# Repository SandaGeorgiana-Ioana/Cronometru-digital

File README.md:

Schema electronică 

Cablaj imprimat

Asamplare PCB

Poza finală după ce am lipit piesele și l-am alimentat

[Documentație.pdf](https://github.com/user-attachments/files/19416694/Documenta.ie.pdf)

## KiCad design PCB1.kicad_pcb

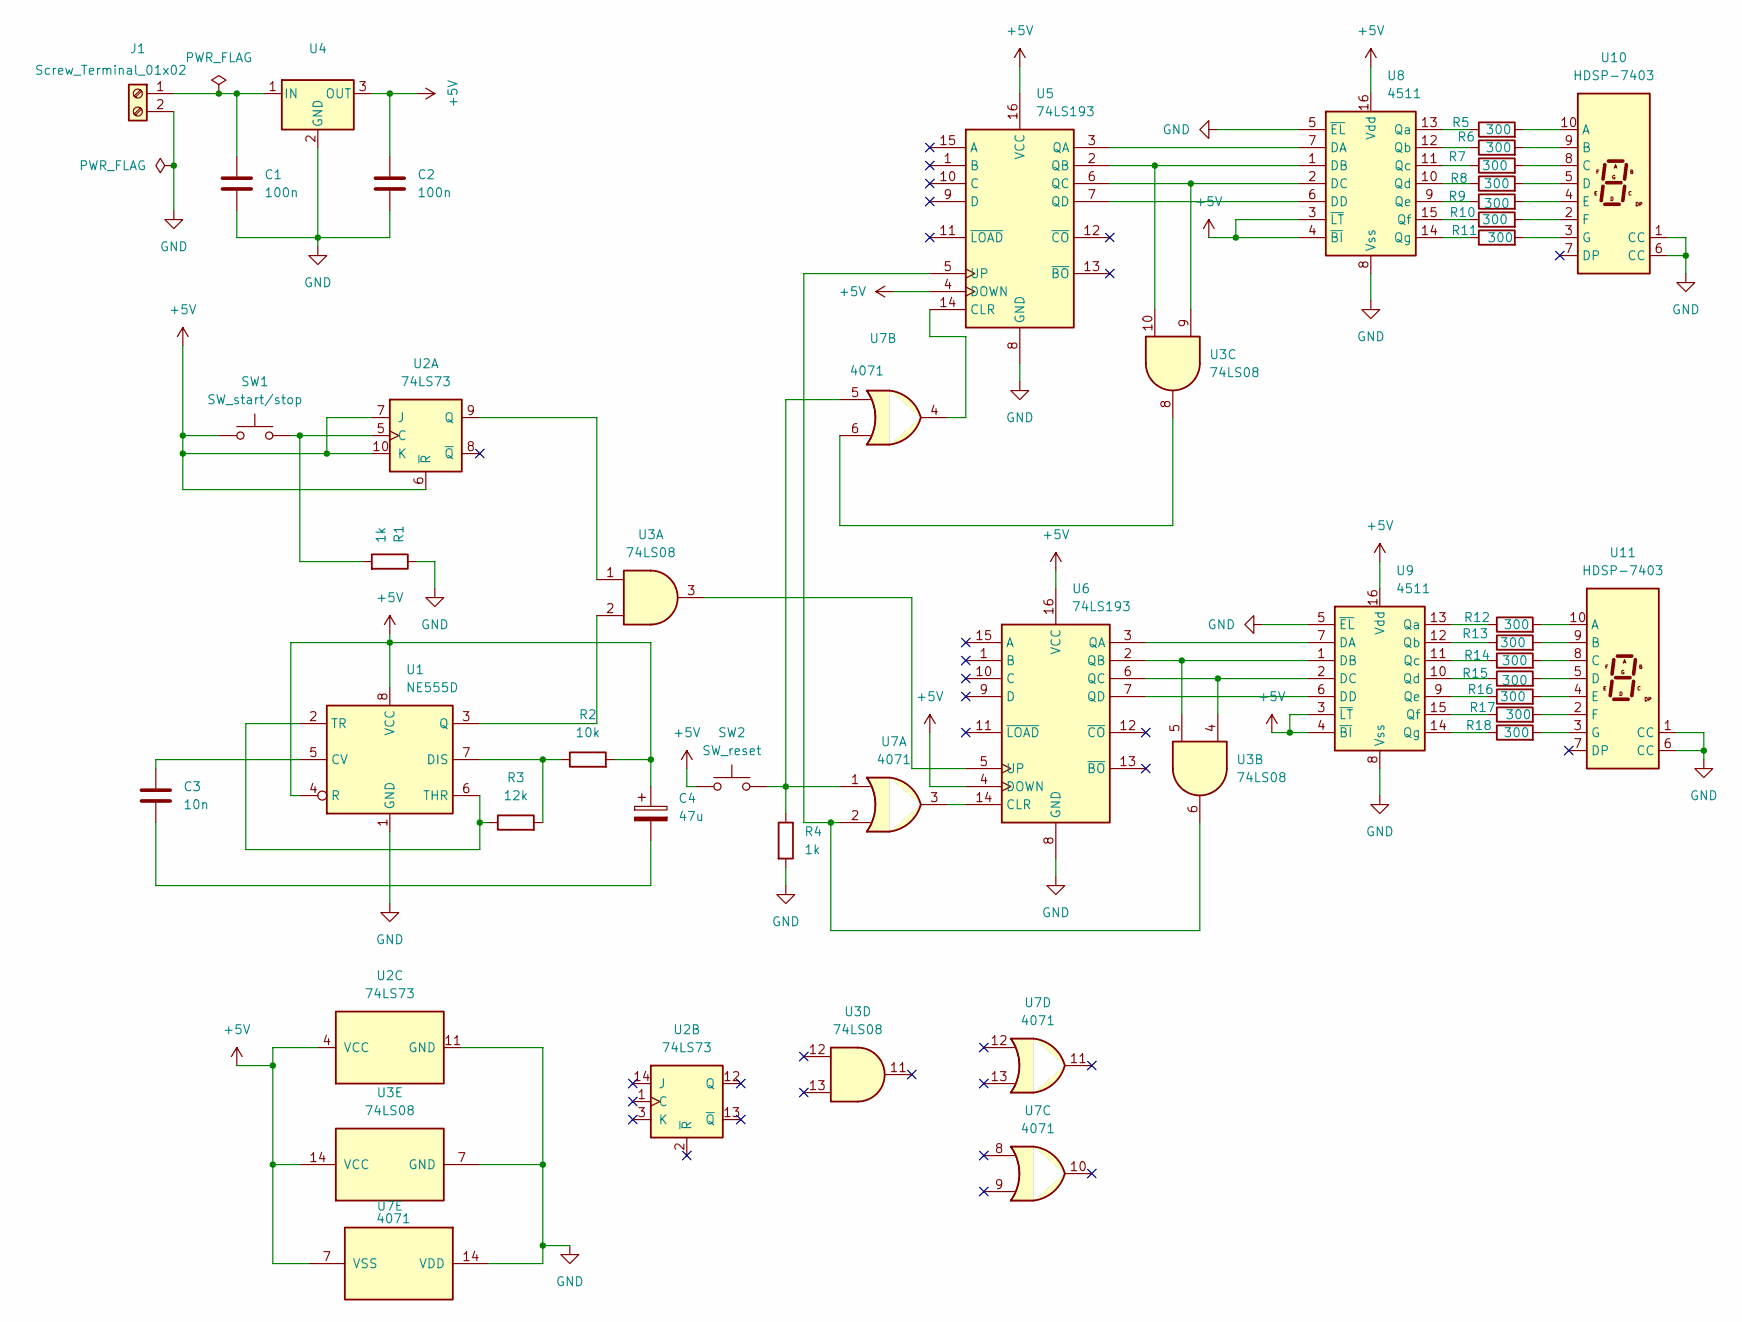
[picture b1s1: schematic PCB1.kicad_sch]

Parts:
C1, C2: 100n; C_Disc_D4.3mm_W1.9mm_P5.00mm
C3: 10n; C_Disc_D4.3mm_W1.9mm_P5.00mm
C4: 47u; C_Radial_D5.0mm_H11.0mm_P2.00mm
J1: Screw_Terminal_01x02; TerminalBlock_Phoenix_MKDS-1,5-2_1x02_P5.00mm_Horizontal
R1, R4: 1k; R_Axial_DIN0309_L9.0mm_D3.2mm_P15.24mm_Horizontal
R2: 10k; R_Axial_DIN0309_L9.0mm_D3.2mm_P12.70mm_Horizontal
R3: 12k; R_Axial_DIN0309_L9.0mm_D3.2mm_P12.70mm_Horizontal
R5, R6, R7, R8, R9, R10, R11, R12, R13, R14, R15, R16, R17, R18: 300; R_Axial_DIN0309_L9.0mm_D3.2mm_P12.70mm_Horizontal
SW1: SW_start/stop; SW_PUSH_6mm
SW2: SW_reset; SW_PUSH_6mm
U1: NE555D; DIP-8_W7.62mm
U2: 74LS73; DIP-14_W7.62mm
U3: 74LS08; DIP-14_W7.62mm
U4: L7805; TO-220-3_Vertical
U5, U6: 74LS193; DIP-16_W7.62mm
U7: 4071; DIP-14_W7.62mm
U8, U9: 4511; DIP-16_W7.62mm
U10, U11: HDSP-7403; HDSP-7401

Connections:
+5V: C2.1, C4.1, R2.2, SW1.1, SW2.1, U1.4 (R), U1.8 (VCC), U2.4 (VCC), U2.6 (~R), U2.7 (J), U2.10 (K), U3.14 (VCC), U4.3 (OUT), U5.4 (DOWN), U5.16 (VCC), U6.4 (DOWN), U6.16 (VCC), U7.7 (VSS), U8.3 (~LT), U8.4 (~BI), U8.16 (Vdd), U9.3 (~LT), U9.4 (~BI), U9.16 (Vdd)
GND: C1.2, C2.2, J1.2, R1.1, R4.2, U1.1 (GND), U2.11 (GND), U3.7 (GND), U4.2 (GND), U5.8 (GND), U6.8 (GND), U7.14 (VDD), U8.5 (~EL), U8.8 (Vss), U9.5 (~EL), U9.8 (Vss), U10.1 (CC), U10.6 (CC), U11.1 (CC), U11.6 (CC)
unnamed: C3.2, C4.2
unnamed: C1.1, J1.1, U4.1 (IN)
unnamed: R4.1, SW2.2, U7.1, U7.5
unnamed: C3.1, U1.5 (CV)
unnamed: R2.1, R3.2, U1.7 (DIS)
unnamed: U1.3 (Q), U3.2
unnamed: R3.1, U1.2 (TR), U1.6 (THR)
unnamed: R1.2, SW1.2, U2.5 (C)
unnamed: U2.9 (Q), U3.1
unnamed: U3.8, U7.6
unnamed: U5.14 (CLR), U7.4
unnamed: U5.3 (QA), U8.7 (DA)
unnamed: U3.10, U5.2 (QB), U8.1 (DB)
unnamed: U3.9, U5.6 (QC), U8.2 (DC)
unnamed: U5.7 (QD), U8.6 (DD)
unnamed: U3.6, U5.5 (UP), U7.2
unnamed: U6.14 (CLR), U7.3
unnamed: U6.3 (QA), U9.7 (DA)
unnamed: U3.5, U6.2 (QB), U9.1 (DB)
unnamed: U3.4, U6.6 (QC), U9.2 (DC)
unnamed: U6.7 (QD), U9.6 (DD)
unnamed: U3.3, U6.5 (UP)
unnamed: R5.1, U8.13 (Qa)
unnamed: R6.1, U8.12 (Qb)
unnamed: R7.1, U8.11 (Qc)
unnamed: R8.1, U8.10 (Qd)
unnamed: R9.1, U8.9 (Qe)
unnamed: R10.1, U8.15 (Qf)
unnamed: R11.1, U8.14 (Qg)
unnamed: R12.1, U9.13 (Qa)
unnamed: R13.1, U9.12 (Qb)
unnamed: R14.1, U9.11 (Qc)
unnamed: R15.1, U9.10 (Qd)
unnamed: R16.1, U9.9 (Qe)
unnamed: R17.1, U9.15 (Qf)
unnamed: R18.1, U9.14 (Qg)
unnamed: R5.2, U10.10 (A)
unnamed: R6.2, U10.9 (B)
unnamed: R7.2, U10.8 (C)
unnamed: R8.2, U10.5 (D)
unnamed: R9.2, U10.4 (E)
unnamed: R10.2, U10.2 (F)
unnamed: R11.2, U10.3 (G)
unnamed: R12.2, U11.10 (A)
unnamed: R13.2, U11.9 (B)
unnamed: R14.2, U11.8 (C)
unnamed: R15.2, U11.5 (D)
unnamed: R16.2, U11.4 (E)
unnamed: R17.2, U11.2 (F)
unnamed: R18.2, U11.3 (G)

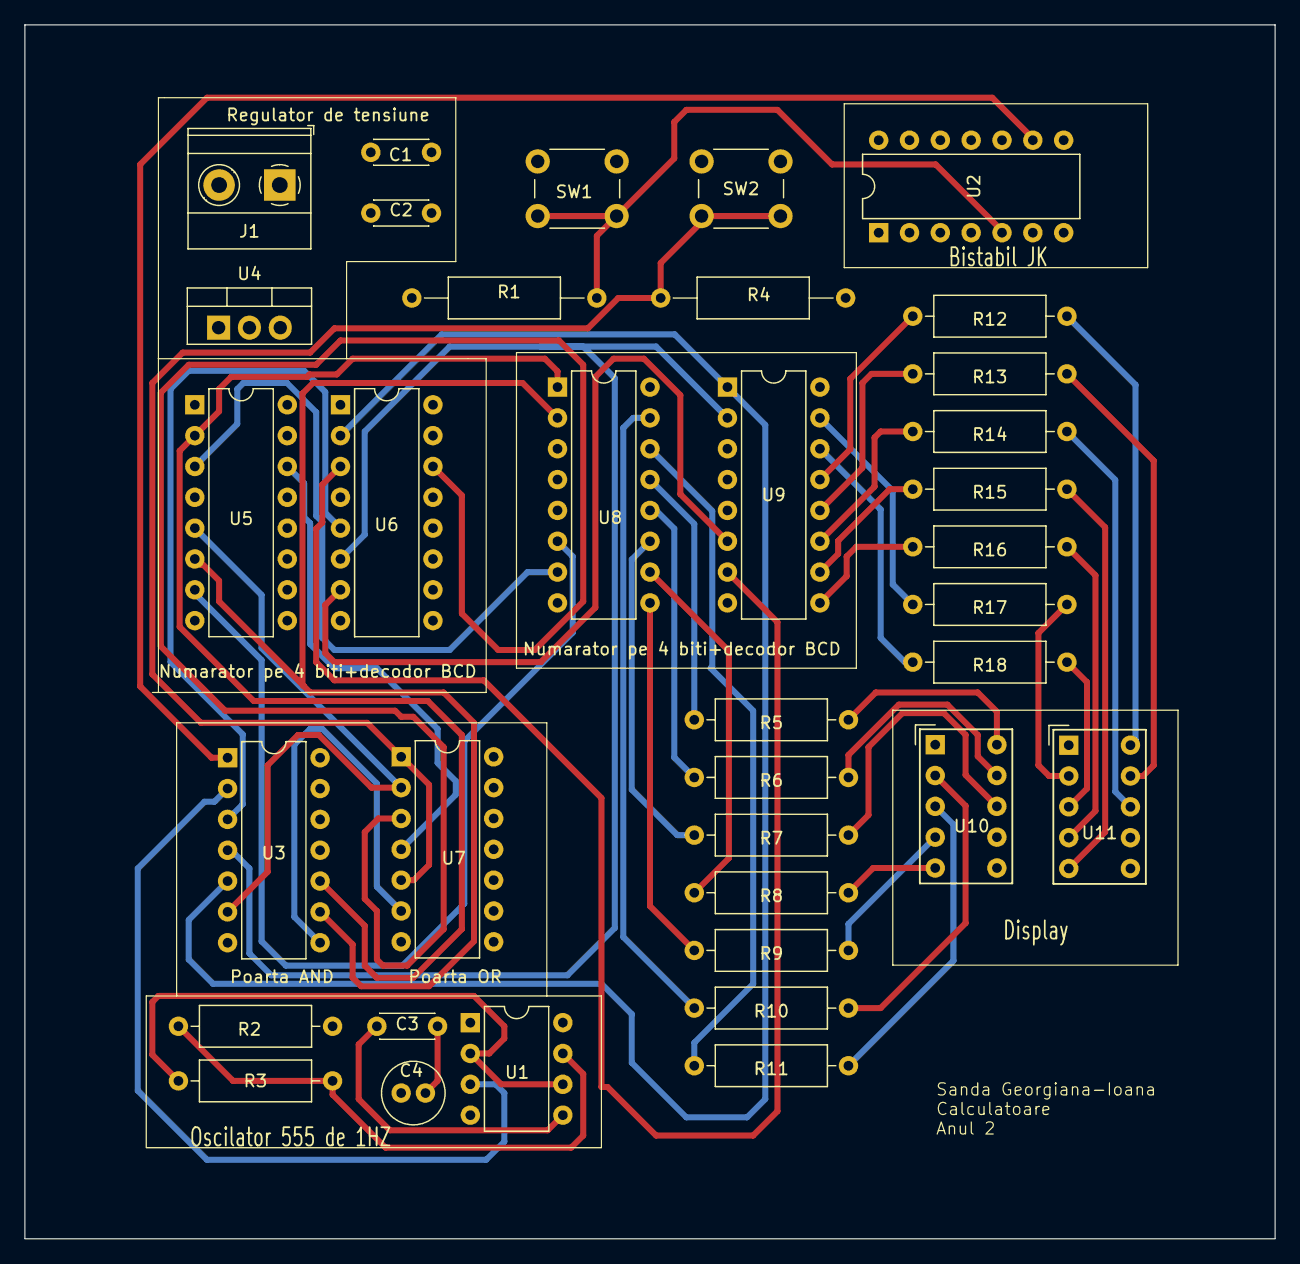
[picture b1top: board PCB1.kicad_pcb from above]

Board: 4 copper layers, 103.0 x 100.0 mm, 36 parts (0 on the bottom side), 52 nets.

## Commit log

2025-03-24 Create README.md
    Documentația proiectului
2025-03-24 Update README.md
    Câteva poze din parcursul proiectului meu și documentația acestuia.
